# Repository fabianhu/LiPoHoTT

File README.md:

LiPoHoTT
========

2S to 6S LiPo monitor for HoTT telemetry.
(c) 2012-2014 Fabian Huslik

order PCBs here:
https://oshpark.com/shared_projects/f62OUvRq

Features:
Optocoupler for communication interface
2-6 Cells
2.54mm pitch connector XH or XT
emulates HoTT GAM
Calibration via full battery
Adjustable alarm levels (2)
External current monitoring possible

Future features:
2-14 in multi-chain-configuration
Configurable as HoTT GAM or EAM
Adjustable alarm delay
Bootloader for field update

This project includes hardware and firmware.

Software released under GPLv3.
Hardware "source code" = .brd & .sch realeased under GPLv3 as well.

Uses code from :

HoTT v4 telemetry for ArduCopter by Adam Majerczyk
printf library by Kustaa Nyholm / SpareTimeLabs
Interrupt UART library by Peter Fleury

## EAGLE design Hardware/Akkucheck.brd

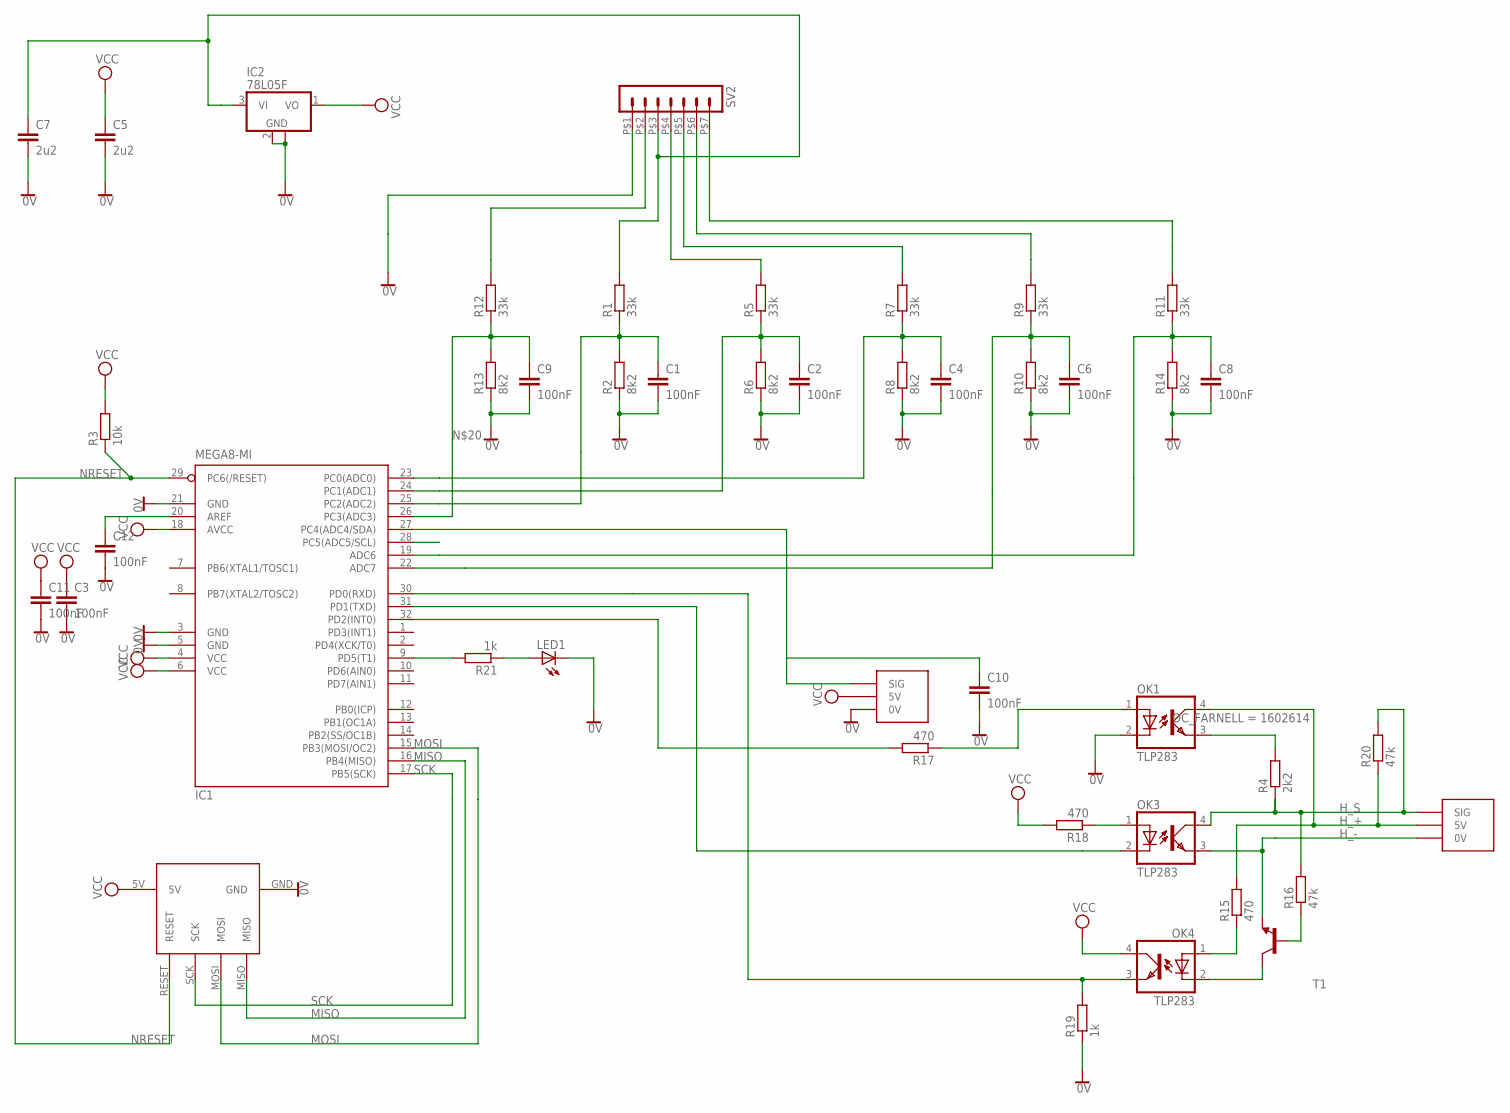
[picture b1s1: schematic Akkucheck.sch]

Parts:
C1, C2, C3, C4, C6, C8, C9, C10, C11, C12: 100nF; C0402; MPN 04023C104KAT2A
C5, C7: 2u2; C0805; MPN MC0805B225K250CT
IC1: MEGA8-MI; MLF32
IC2: 78L05F; SOT89; MPN L78L05ABUTR
IN1, IN3: 3-WIRE_CONNWIRE; 3WIRE_CONN
LED1: LEDCHIPLED_0603; CHIPLED_0603
OK1, OK3, OK4: TLP283; MINI-FLAT-4; MPN ACPL-217-500E
R1, R5, R7, R9, R11, R12: 33k; R0402; MPN CRG0402F33K
R2, R6, R8, R10, R13, R14: 8k2; R0402; MPN CRG0402F8K2
R3: 10k; R0402; MPN CRCW040210K0FKEAHP
R4: 2k2; R0402; MPN ERJ2GEJ222X
R15, R17, R18: 470; R0402; MPN ERJ2GEJ470X
R16, R20: 47k; R0402; MPN ERJ2GEJ473X
R19, R21: 1k; R0402; MPN ERJ2GEJ102X
SV2: MA07-1_SMD
T1: BC817-16-NPN-SOT23-BEC; SOT23-BEC; MPN BC817,215
U$1: ISPSMD; ISP_SMD

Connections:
0V: C1.2, C2.2, C3.2, C4.2, C5.2, C6.2, C7.2, C8.2, C9.2, C10.2, C11.2, C12.2, IC1.3 (GND), IC1.5 (GND), IC1.21 (GND), IC2.2 (GND), IC2.2@1 (GND), IN1.0V, LED1.C, OK1.2 (C), R2.1, R6.1, R8.1, R10.1, R13.1, R14.1, R19.1, SV2.P$1 (1), U$1.GND
H_+: IN3.5V, OK1.4 (COL), R15.2, R20.1
H_-: IN3.0V, OK3.3 (EMIT), T1.E
H_S: IN3.SIG, OK3.4 (COL), R4.1, R16.2, R20.2
MISO: IC1.16 (PB4(MISO)), U$1.MISO
MOSI: IC1.15 (PB3(MOSI/OC2)), U$1.MOSI
unnamed: R12.2, SV2.P$2 (2)
unnamed: C6.1, IC1.22 (ADC7), R9.1, R10.2
unnamed: R5.2, SV2.P$4 (4)
unnamed: R7.2, SV2.P$5 (5)
unnamed: R9.2, SV2.P$6 (6)
unnamed: C10.1, IC1.27 (PC4(ADC4/SDA)), IN1.SIG
unnamed: C7.1, IC2.3 (VI), R1.2, SV2.P$3 (3)
unnamed: C8.1, IC1.19 (ADC6), R11.1, R14.2
unnamed: LED1.A, R21.1
unnamed: IC1.9 (PD5(T1)), R21.2
unnamed: OK1.3 (EMIT), R4.2
unnamed: OK4.1 (A), R15.1
unnamed: OK4.2 (C), T1.C
unnamed: C1.1, IC1.25 (PC2(ADC2)), R1.1, R2.2
unnamed: C2.1, IC1.24 (PC1(ADC1)), R5.1, R6.2
unnamed: IC1.30 (PD0(RXD)), OK4.3 (EMIT), R19.2
unnamed: IC1.31 (PD1(TXD)), OK3.2 (C)
unnamed: C9.1, IC1.26 (PC3(ADC3)), R12.1, R13.2
unnamed: R16.1, T1.B
unnamed: OK3.1 (A), R18.1
unnamed: IC1.32 (PD2(INT0)), R17.2
unnamed: OK1.1 (A), R17.1
unnamed: C12.1, IC1.20 (AREF)
unnamed: R11.2, SV2.P$7 (7)
unnamed: C4.1, IC1.23 (PC0(ADC0)), R7.1, R8.2
NRESET: IC1.29 (PC6(/RESET)), R3.1, U$1.RESET
SCK: IC1.17 (PB5(SCK)), U$1.SCK
VCC: C3.1, C5.1, C11.1, IC1.4 (VCC), IC1.6 (VCC), IC1.18 (AVCC), IC2.1 (VO), IN1.5V, OK4.4 (COL), R3.2, R18.2, U$1.5V

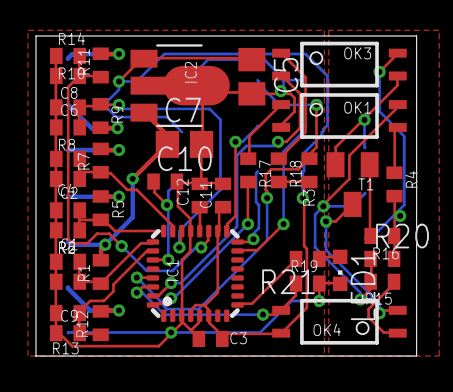
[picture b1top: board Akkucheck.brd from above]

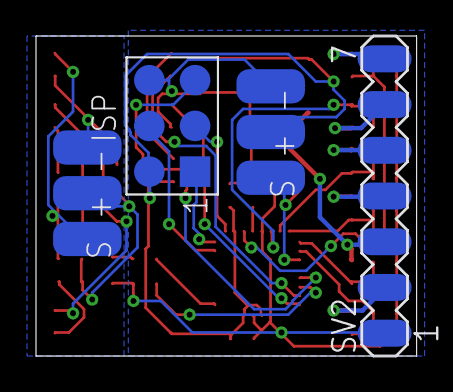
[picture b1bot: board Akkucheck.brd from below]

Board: 2 copper layers, 21.1 x 17.8 mm, 44 parts (4 on the bottom side), 34 nets.

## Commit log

2014-05-03 added all files
2014-05-22 added multi-doc
2014-06-05 updated hardware+ - changed extension pin - out supply to cell 2
2014-11-11 added ignores
2015-06-14 optimized for production at OSHpark
2015-06-14 optimized timer stuff
2015-06-15 add compiler requirement as comment
    With the new compiler the text mode does not work.
2015-08-02 updated BOM
2024-09-14 screenshots from old homepage
